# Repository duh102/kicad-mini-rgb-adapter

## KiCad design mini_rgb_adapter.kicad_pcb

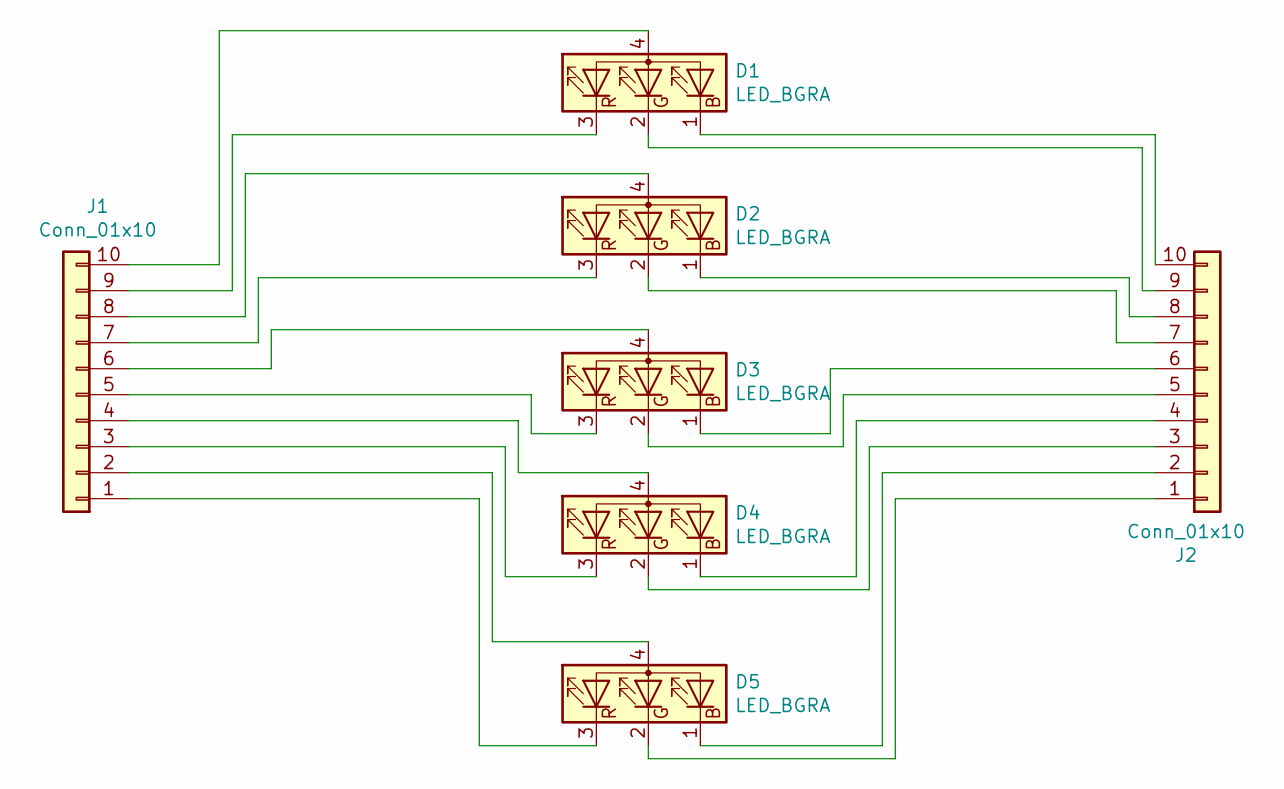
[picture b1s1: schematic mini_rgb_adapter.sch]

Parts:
D1, D2, D3, D4, D5: LED_BGRA; LED_Cree-UHD1110-FKA_1x1mm
J1, J2: Conn_01x10; PinHeader_1x10_P2.54mm_Vertical

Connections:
unnamed: D1.1 (BK), J2.10
unnamed: D1.2 (GK), J2.9
unnamed: D1.3 (RK), J1.9
unnamed: D1.4 (A), J1.10
unnamed: D2.1 (BK), J2.8
unnamed: D2.2 (GK), J2.7
unnamed: D2.3 (RK), J1.7
unnamed: D2.4 (A), J1.8
unnamed: D3.1 (BK), J2.6
unnamed: D3.2 (GK), J2.5
unnamed: D3.3 (RK), J1.5
unnamed: D3.4 (A), J1.6
unnamed: D4.1 (BK), J2.4
unnamed: D4.2 (GK), J2.3
unnamed: D4.3 (RK), J1.3
unnamed: D4.4 (A), J1.4
unnamed: D5.1 (BK), J2.2
unnamed: D5.2 (GK), J2.1
unnamed: D5.3 (RK), J1.1
unnamed: D5.4 (A), J1.2

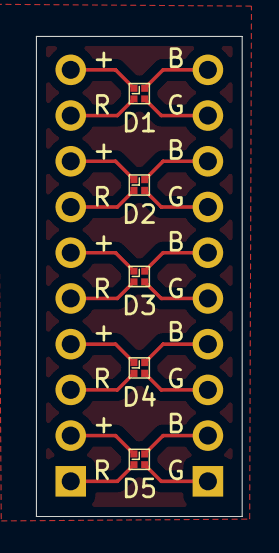
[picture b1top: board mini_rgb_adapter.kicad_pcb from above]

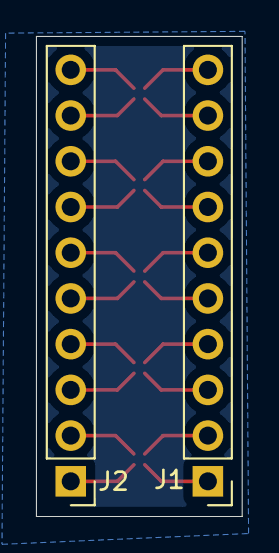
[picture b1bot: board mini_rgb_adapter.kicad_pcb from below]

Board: 2 copper layers, 11.4 x 26.7 mm, 7 parts (2 on the bottom side), 20 nets.
